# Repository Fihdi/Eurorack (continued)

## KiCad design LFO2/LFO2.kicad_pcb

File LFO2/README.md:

# Voltage controllable LFO/VCO

The core oscillator of this circuit is the same as in my TRIVCO module, an OTA-based relaxation oscillator, so this module can be used as a VCO as well.

The triangle output is strictly above 0V while the inverted triangle output is centered to 0V. The triangle output is strictly positive so I can reliably pull it down to 0V with the RESET input.

No more shape control, only way to get a sawtooth signal is to connect its square-wave output into the RESET input.

The module that you see in the picture above is using circuit boards that were fabricated by [PCBWay](https://www.pcbway.com/). They have excellent build quality and I can recommend using their service to build your own projects! I used the "Black" option for the soldermask and the surface has very deep and glossy black finish, which looks amazing, they also have an option for a "Matte Black" finish which I will try next time. Thank you PCBWay for sponsoring this module. Their website is very intuitive to use, just upload the gerber files as a .zip-file, tick the options such as base material, board width, my favorite feature: separate colors for the soldermask and silkscreen, surface finish etc. With multiple options for payment and fast delivery fast times I was able to put the entire project together in less than one month.

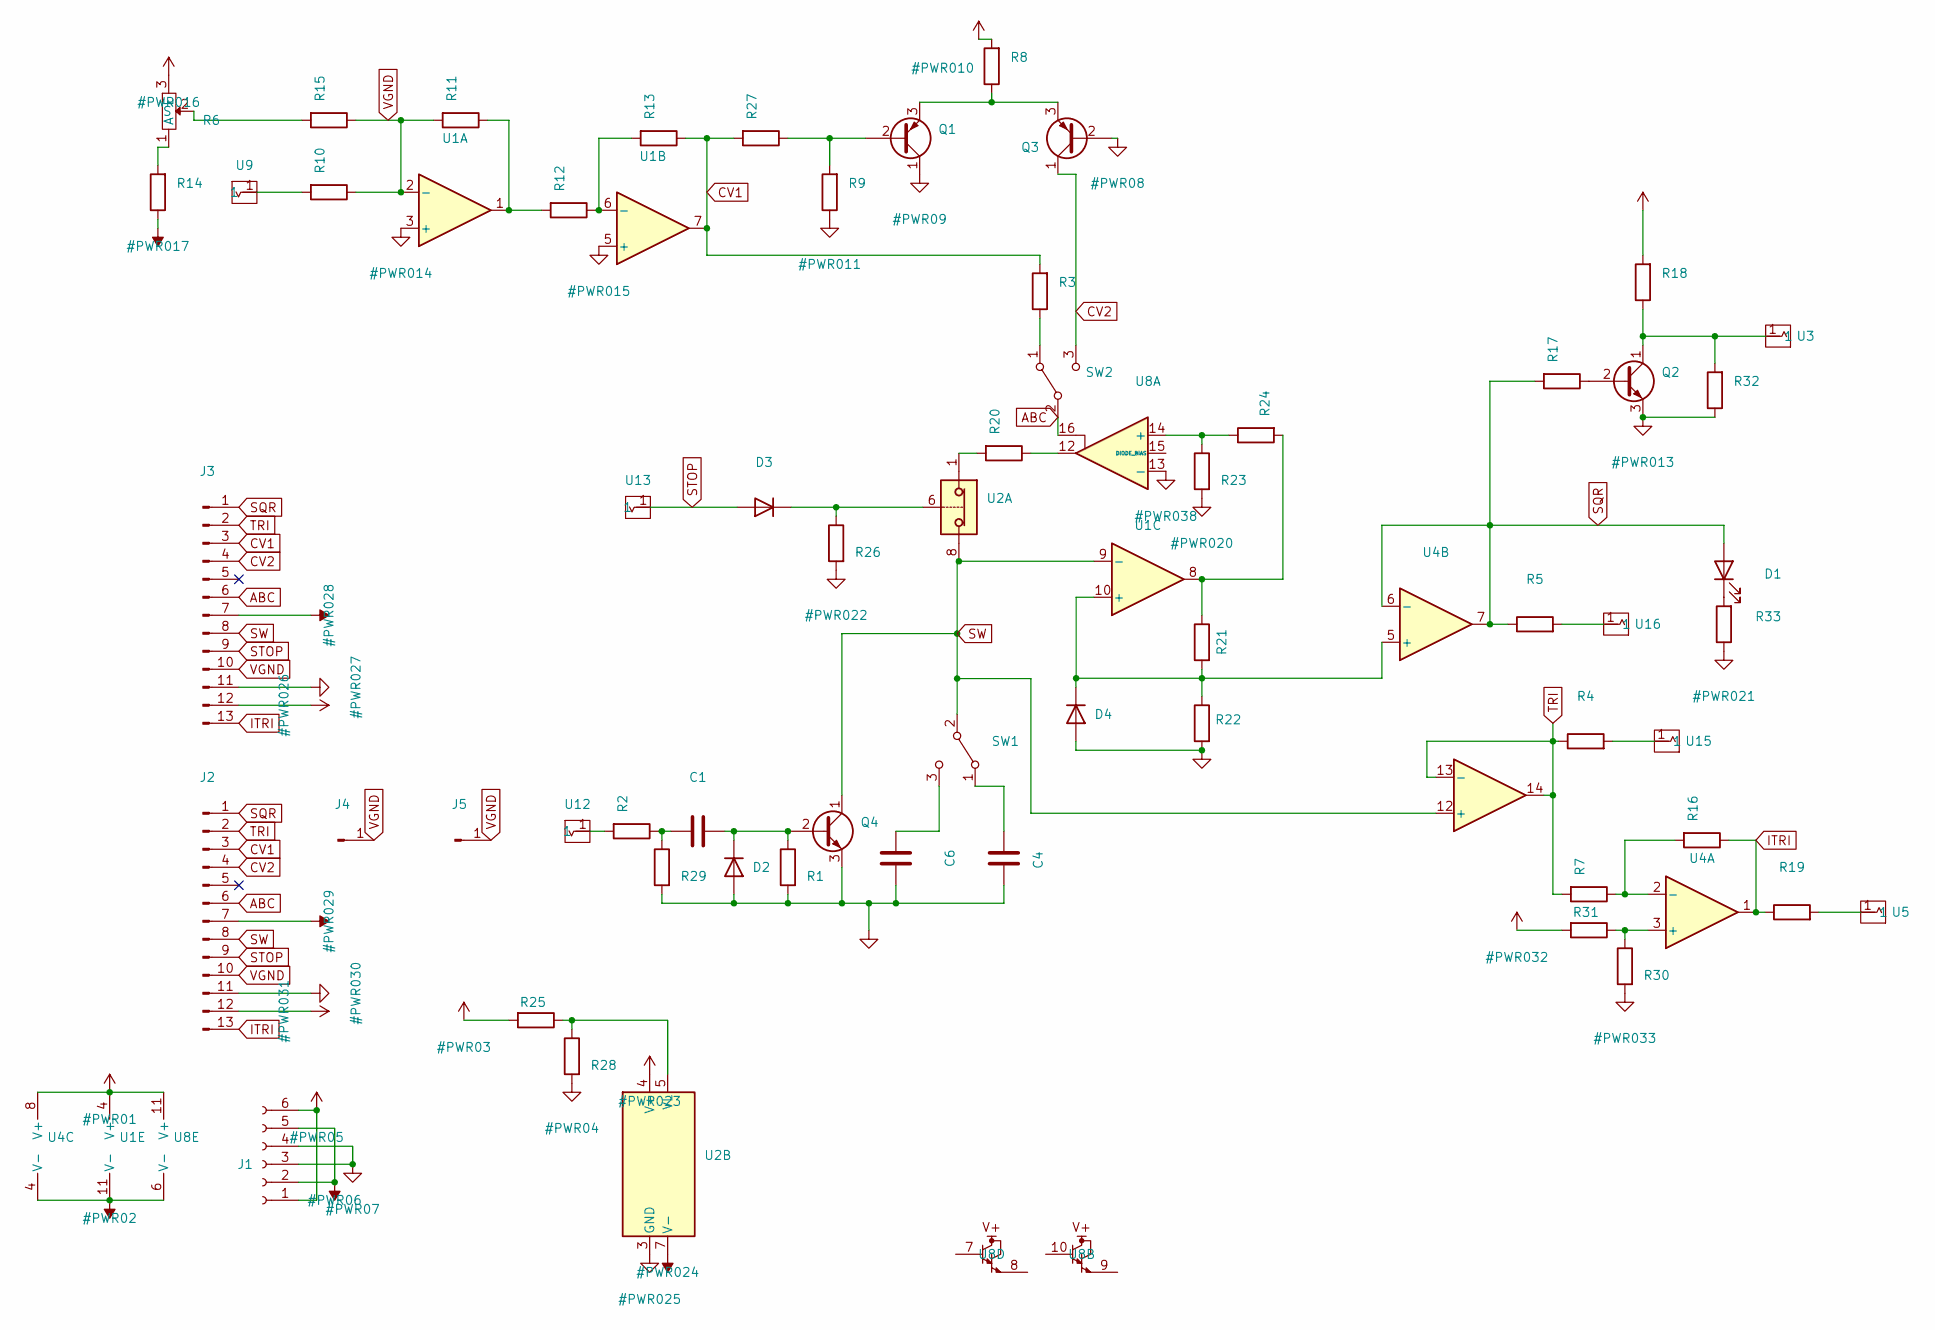
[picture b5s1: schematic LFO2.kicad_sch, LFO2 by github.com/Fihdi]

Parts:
C1, C4, C6: C; C_Axial_L3.8mm_D2.6mm_P10.00mm_Horizontal
D1: LED; LED_D5.0mm
D2, D3, D4: D; D_A-405_P7.62mm_Horizontal
J1: Conn_01x06_Female; PinHeader_1x06_P2.54mm_Vertical
J2, J3: Conn_01x13_Pin; PinHeader_1x13_P2.54mm_Vertical
J4, J5: Conn_01x01_Pin; PinHeader_1x01_P2.54mm_Vertical
Q1, Q3: BC557; TO-92L_Wide
Q2, Q4: BC547; TO-92L_Inline_Wide
R1, R7, R10, R11, R12, R13, R15, R16, R17, R21, R22, R24, R25, R26, R28, R29, R30, R31: 100k; R_Axial_DIN0204_L3.6mm_D1.6mm_P7.62mm_Horizontal
R2, R9, R14, R18, R20, R27, R32, R33: 4k7; R_Axial_DIN0204_L3.6mm_D1.6mm_P7.62mm_Horizontal
R3, R8: 10k; R_Axial_DIN0204_L3.6mm_D1.6mm_P7.62mm_Horizontal
R4, R5, R19, R23: 1k; R_Axial_DIN0204_L3.6mm_D1.6mm_P7.62mm_Horizontal
R6: 50k; AlpsPot
SW1, SW2: SW_SPDT; Switch
U1: TL074; DIP-14_W7.62mm
U2: DG417xJ; DIP-8_W7.62mm
U3, U5, U9, U12, U13, U15, U16: Aux_flush; 3mm5 Mono Aux
U4: TL072; DIP-8_W7.62mm
U8: LM13700; DIP-16_W7.62mm

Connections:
+12V: J1.1, J1.6, J2.12, J3.12, R6.3 (E), R8.2, R18.2, R25.2, R31.2, U1.4 (V+), U2.4 (V+), U4.8 (V+), U8.11 (V+)
-12V: J1.2, J1.5, J2.7, J3.7, R14.1, U1.11 (V-), U2.7 (V-), U4.4 (V-), U8.6 (V-)
ABC: J2.6, J3.6, SW2.2 (B), U8.16
CV1: J2.3, J3.3, R3.2, R13.1, R27.2, U1.7
CV2: J2.4, J3.4, Q3.1 (C), SW2.3 (C)
GND: C4.2, C6.2, D2.2 (A), D4.2 (A), J1.3, J1.4, J2.11, J3.11, Q1.1 (C), Q2.3 (E), Q3.2 (B), Q4.3 (E), R1.2, R9.1, R22.2, R23.2, R26.2, R28.2, R29.2, R30.2, R32.1, R33.1, U1.3 (+), U1.5 (+), U2.3 (GND), U8.13 (-)
ITRI: J2.13, J3.13, R16.1, R19.1, U4.1
unnamed: C1.1, R2.1, R29.1
unnamed: D1.1 (K), R33.2
unnamed: C1.2, D2.1 (K), Q4.2 (B), R1.1
unnamed: D3.1 (K), R26.1, U2.6
unnamed: D4.1 (K), R21.2, R22.1, U1.10 (+), U4.5 (+)
unnamed: Q1.2 (B), R9.2, R27.1
unnamed: Q1.3 (E), Q3.3 (E), R8.1
unnamed: Q2.2 (B), R17.1
unnamed: Q2.1 (C), R18.1, R32.2, U3.1
unnamed: R2.2, U12.1
unnamed: R4.2, U15.1
unnamed: R5.2, U16.1
unnamed: R6.1 (A), R14.2
unnamed: R6.2 (S), R15.2
unnamed: R10.2, U9.1
unnamed: R11.1, R12.2, U1.1
unnamed: R19.2, U5.1
unnamed: R20.1, U8.12
unnamed: R20.2, U2.1
unnamed: R21.1, R24.2, U1.8
unnamed: C4.1, SW1.1 (A)
unnamed: C6.1, SW1.3 (C)
unnamed: R3.1, SW2.1 (A)
unnamed: R12.1, R13.2, U1.6 (-)
unnamed: R25.1, R28.1, U2.5 (VL)
unnamed: R30.1, R31.1, U4.3 (+)
unnamed: R7.1, R16.2, U4.2 (-)
unnamed: R23.1, R24.1, U8.14 (+)
SQR: D1.2 (A), J2.1, J3.1, R5.1, R17.2, U4.6 (-), U4.7
STOP: D3.2 (A), J2.9, J3.9, U13.1
SW: J2.8, J3.8, Q4.1 (C), SW1.2 (B), U1.9 (-), U1.12 (+), U2.8
TRI: J2.2, J3.2, R4.1, R7.2, U1.13 (-), U1.14
VGND: J2.10, J3.10, J4.1, J5.1, R10.1, R11.2, R15.1, U1.2 (-)

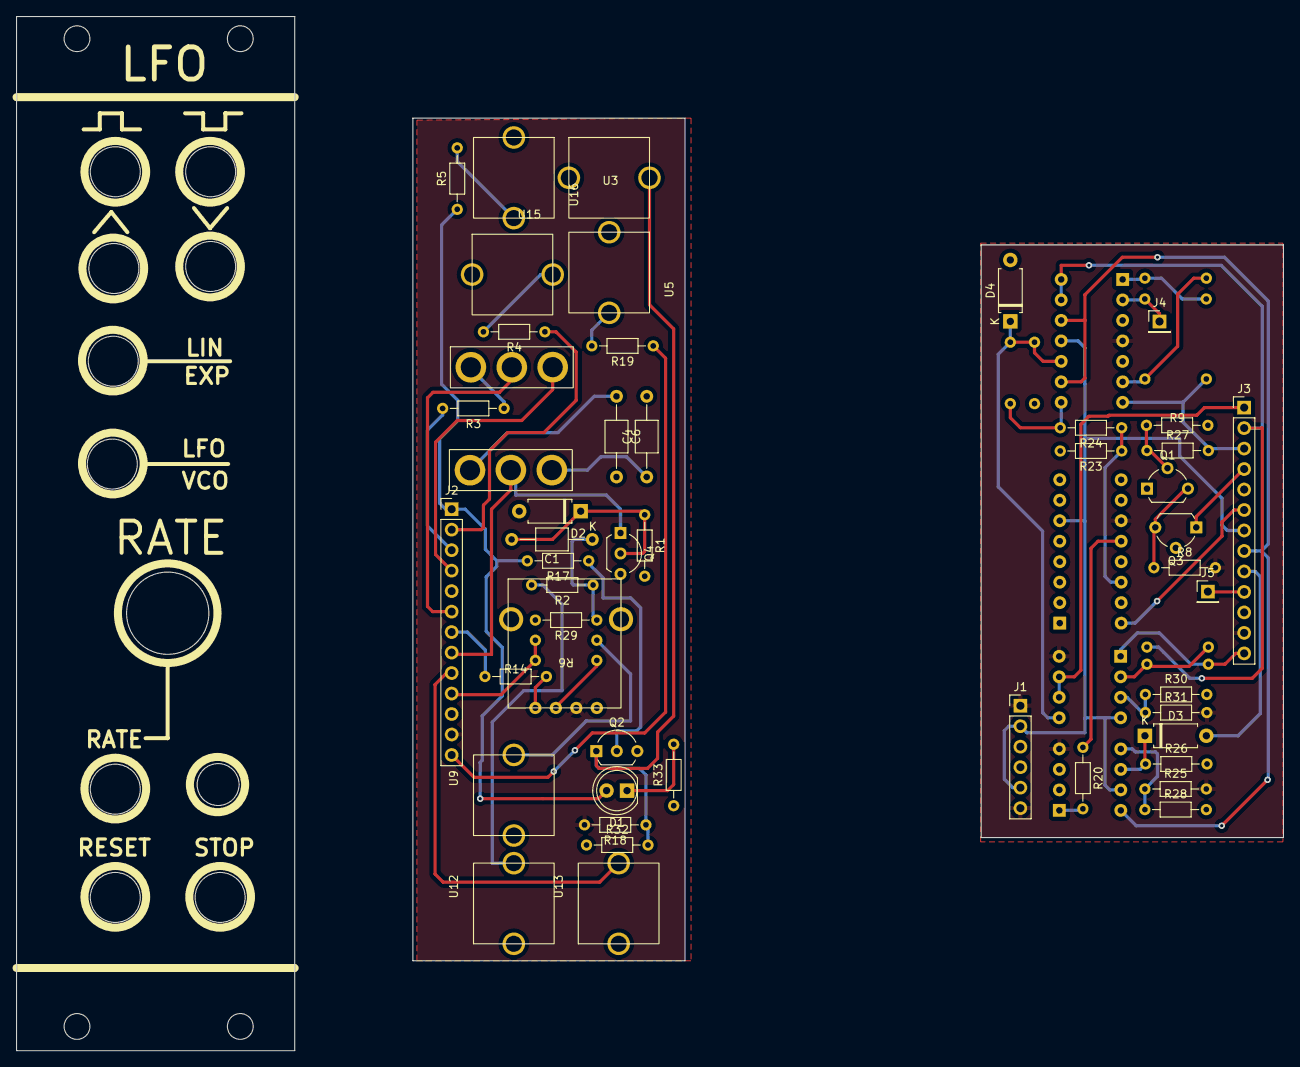
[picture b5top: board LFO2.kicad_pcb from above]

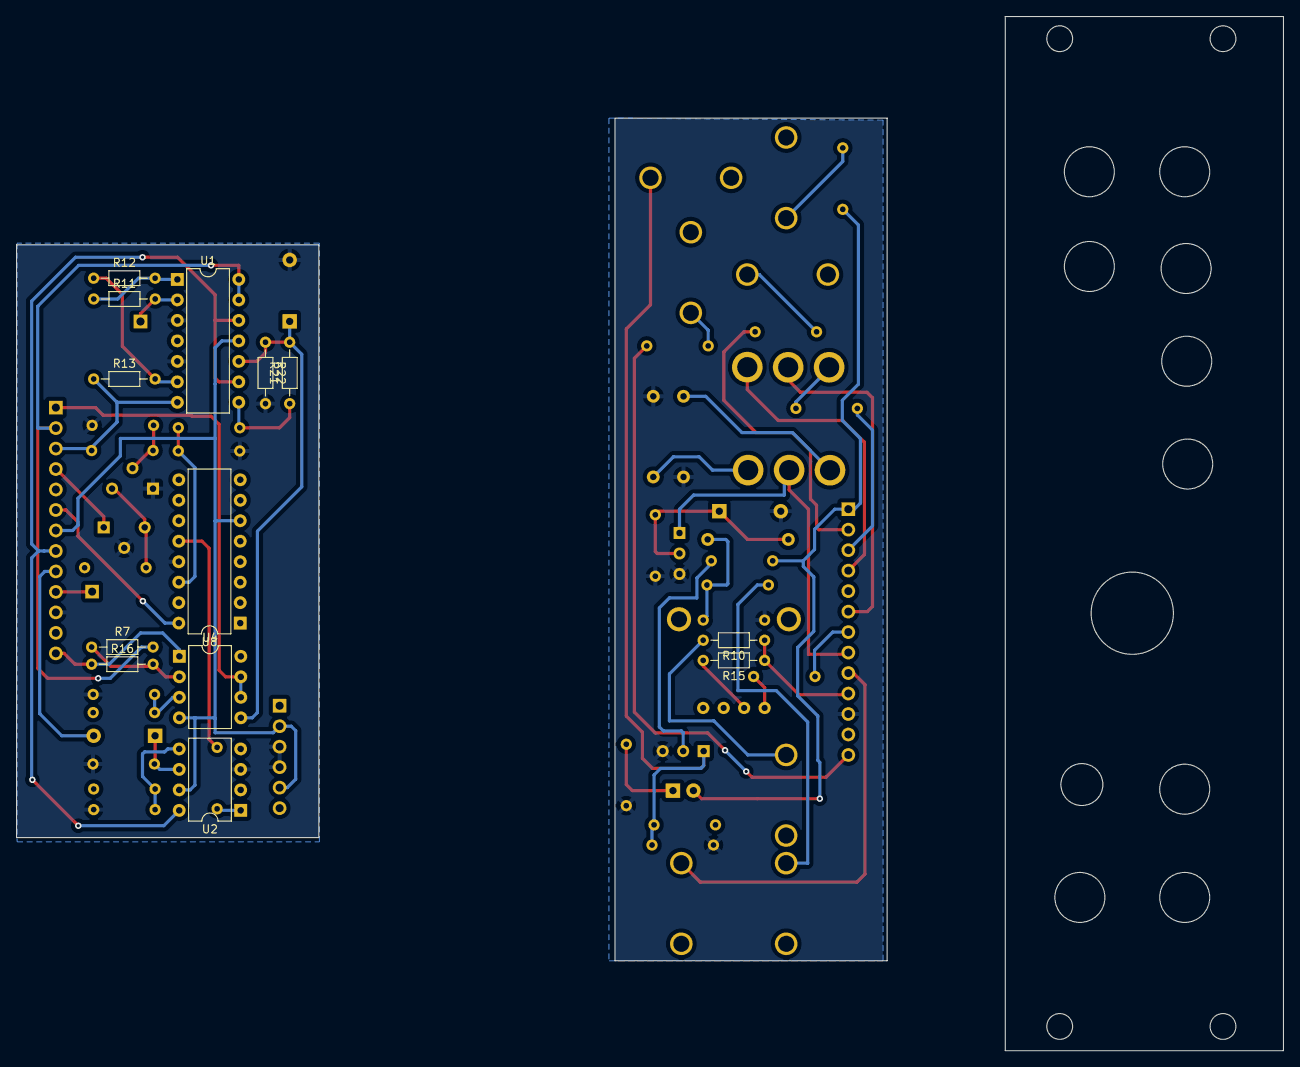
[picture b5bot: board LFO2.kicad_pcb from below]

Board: 2 copper layers, 157.1 x 128.2 mm, 62 parts (13 on the bottom side), 40 nets.

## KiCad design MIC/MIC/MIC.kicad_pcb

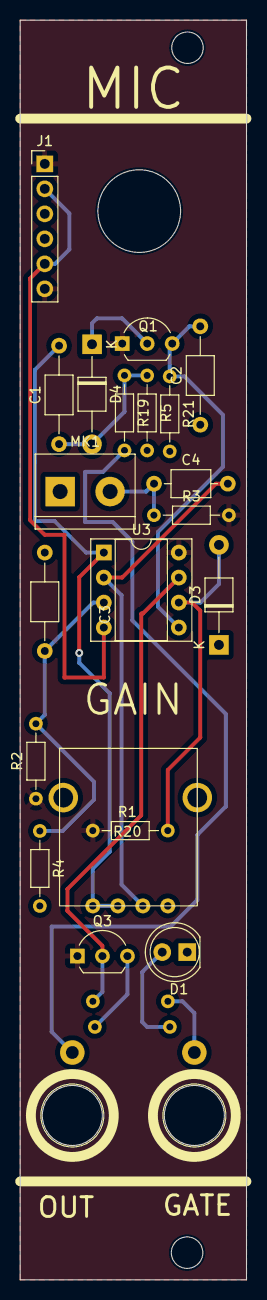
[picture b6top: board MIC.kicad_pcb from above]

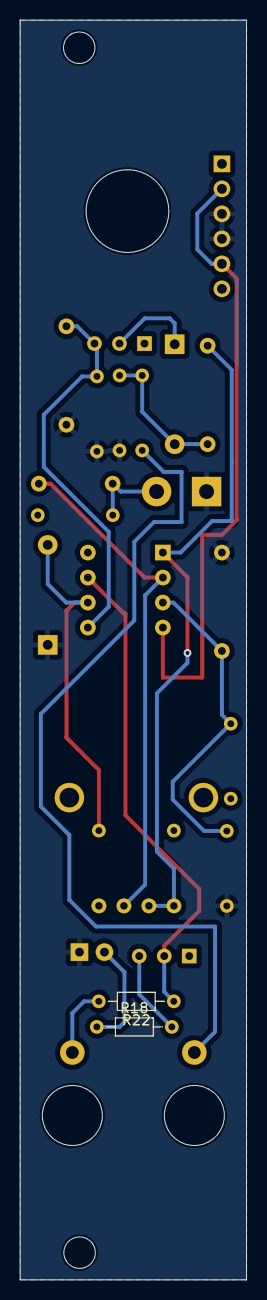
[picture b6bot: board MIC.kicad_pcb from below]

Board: 2 copper layers, 23.0 x 128.0 mm, 24 parts (2 on the bottom side), 16 nets.

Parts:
C1, C2, C3: C; C_Axial_L3.8mm_D2.6mm_P10.00mm_Horizontal
C4: C; C_Axial_L3.8mm_D2.6mm_P7.50mm_Horizontal
D1: LED; LED_D5.0mm
D3, D4: D; D_T-1_P10.16mm_Horizontal
J1: Conn_01x06_Pin; PinHeader_1x06_P2.54mm_Vertical
MK1: Microphone; TerminalBlock_bornier-2_P5.08mm
Q1, Q3: BC547; TO-92L_Inline_Wide
R1: AlpsPot
R2, R3, R4, R5, R18, R19, R20, R21, R22: R; R_Axial_DIN0204_L3.6mm_D1.6mm_P7.62mm_Horizontal
U1, U2: Aux_flush; aux_flush
U3: TL072; DIP-8_W7.62mm_Socket

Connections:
+12V: J1.1, J1.6, Q1.1 (C), Q3.1 (C), R2.1, R3.2, R20.2, U3.8 (V+)
-12V: J1.2, J1.5, U3.4 (V-)
GND: C2.1, C3.1, D1.1 (K), D3.1 (K), J1.3, J1.4, MK1.1 (-), R4.2, R5.2, R21.2
unnamed: D1.2 (A), R18.1
unnamed: D3.2 (A), R20.1, U3.6 (-)
unnamed: C1.1, D4.2 (A), R5.1, R19.1
unnamed: D4.1 (K), Q1.2 (B)
unnamed: C4.1, MK1.2 (+), R3.1
unnamed: C2.2, Q1.3 (E), R21.1, U3.5 (+)
unnamed: Q3.2 (B), R22.1, U3.7
unnamed: Q3.3 (E), R18.2
unnamed: C1.2, R1.1 (A), R1.2 (S), U3.1
unnamed: C4.2, R1.3 (E), U3.2 (-)
unnamed: R19.2, U1.1
unnamed: R22.2, U2.1
unnamed: C3.2, R2.2, R4.1, U3.3 (+)

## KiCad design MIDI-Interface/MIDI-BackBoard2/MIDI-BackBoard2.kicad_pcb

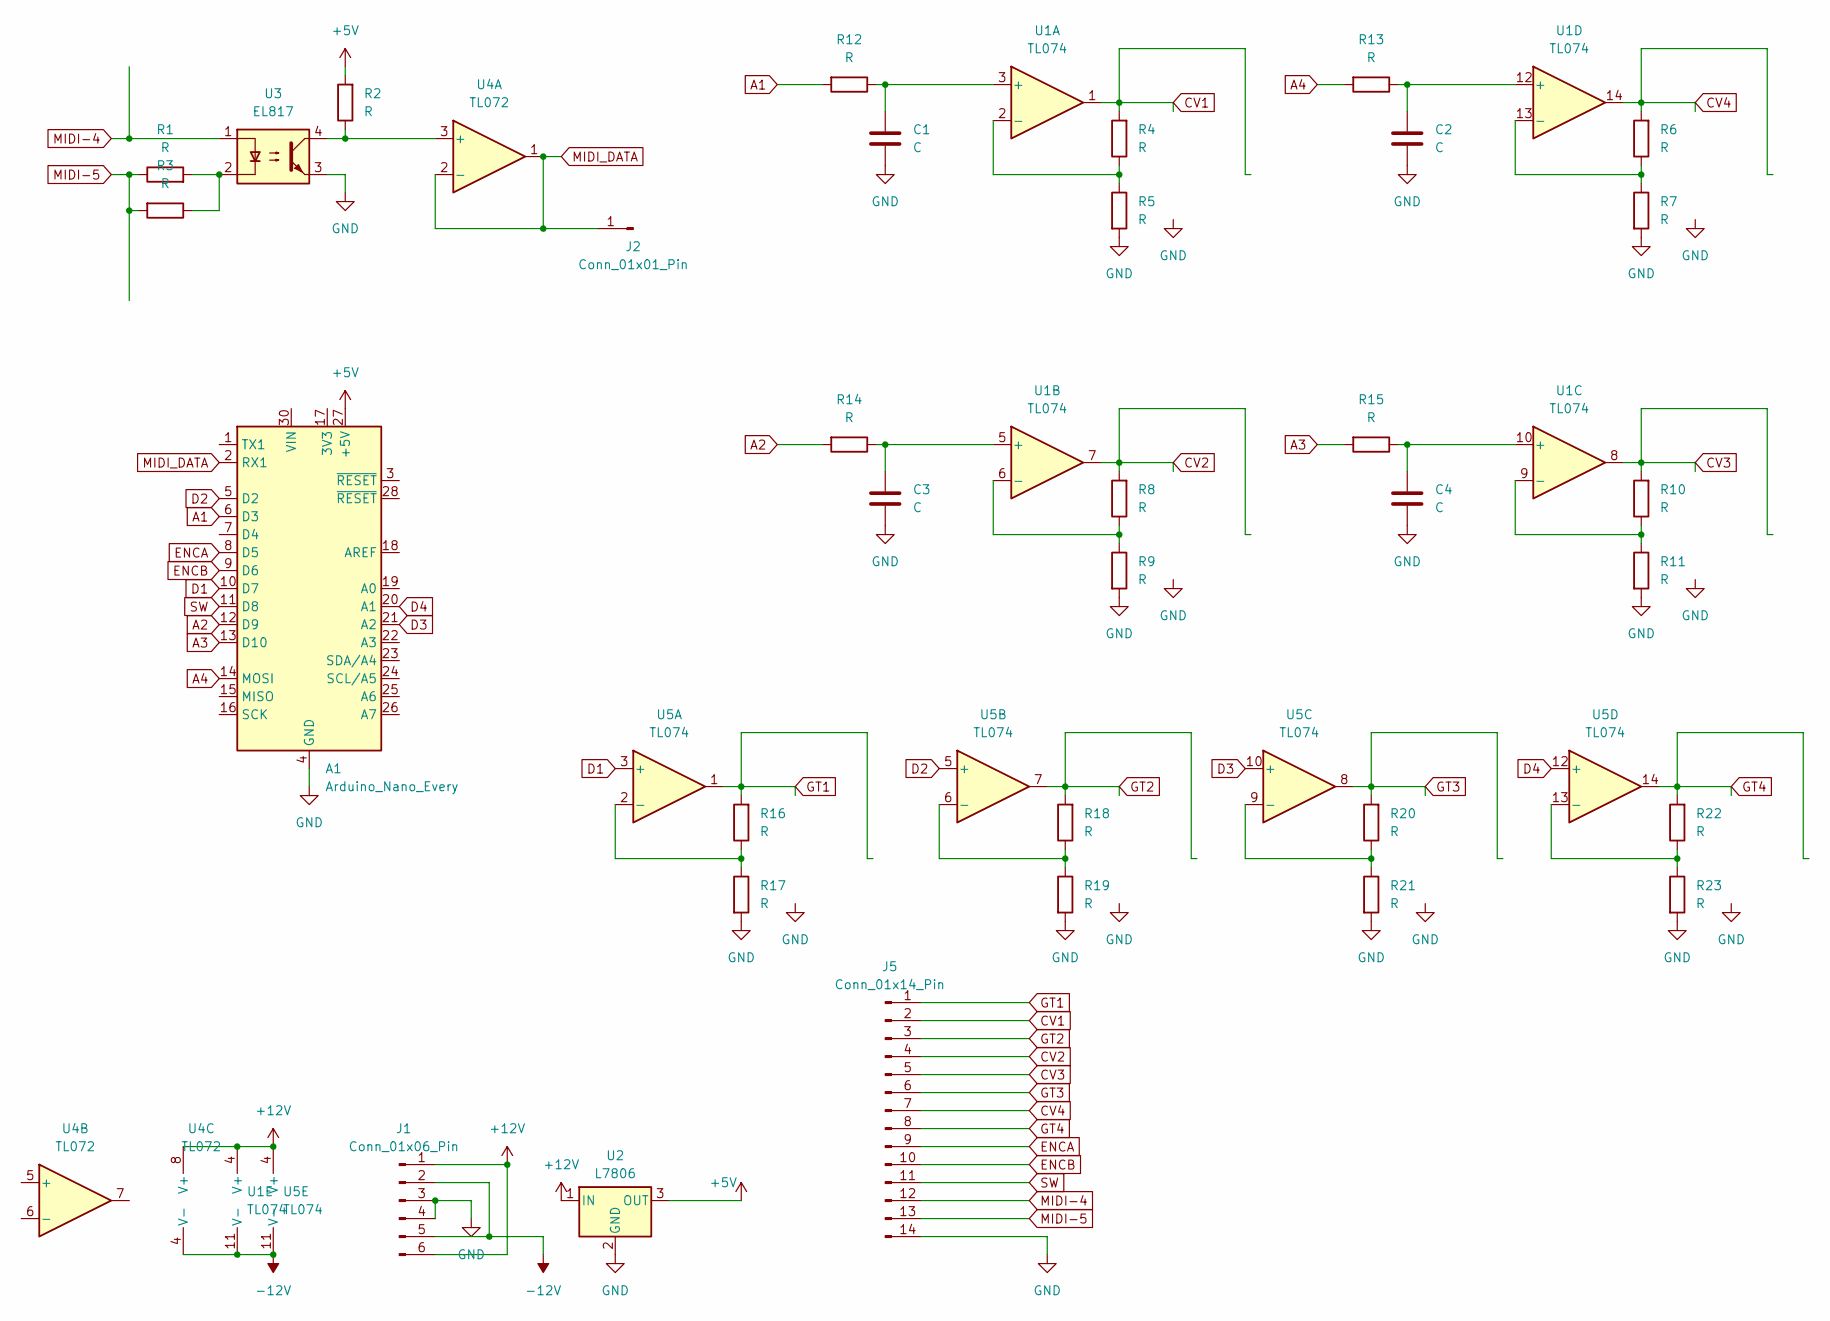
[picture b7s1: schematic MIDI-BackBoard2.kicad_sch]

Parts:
A1: Arduino_Nano_Every; Arduino_Nano
C1, C2, C3, C4: C; C_Rect_L7.0mm_W2.5mm_P5.00mm
J1: Conn_01x06_Pin; PinSocket_1x06_P2.54mm_Vertical
J2: Conn_01x01_Pin; PinHeader_1x01_P2.54mm_Vertical
J5: Conn_01x14_Pin; PinHeader_1x14_P2.54mm_Vertical
R1, R2, R3, R4, R5, R6, R7, R8, R9, R10, R11, R12, R13, R14, R15, R16, R17, R18, R19, R20, R21, R22, R23: R; R_Axial_DIN0207_L6.3mm_D2.5mm_P7.62mm_Horizontal
U1: TL074; DIP-14_W7.62mm_Socket
U2: L7806; TO-252-3_TabPin2
U3: EL817; DIP-4_W7.62mm
U4: TL072; DIP-8_W7.62mm
U5: TL074; DIP-14_W7.62mm

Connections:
+5V: A1.27 (+5V), R2.2, U2.3 (OUT)
+12V: J1.1, J1.6, U1.4 (V+), U2.1 (IN), U4.8 (V+), U5.4 (V+)
-12V: J1.2, J1.5, U1.11 (V-), U4.4 (V-), U5.11 (V-)
A1: A1.6 (D3), R12.2
A2: A1.12 (D9), R14.2
A3: A1.13 (D10), R15.2
A4: A1.14 (MOSI), R13.2
CV1: J5.2, R4.2, U1.1
CV2: J5.4, R8.2, U1.7
CV3: J5.5, R10.2, U1.8
CV4: J5.7, R6.2, U1.14
D1: A1.10 (D7), U5.3 (+)
D2: A1.5 (D2), U5.5 (+)
D3: A1.21 (A2), U5.10 (+)
D4: A1.20 (A1), U5.12 (+)
ENCA: A1.8 (D5), J5.9
ENCB: A1.9 (D6), J5.10
GND: A1.4 (GND), A1.29 (GND), C1.2, C2.2, C3.2, C4.2, J1.3, J1.4, J5.14, R5.2, R7.2, R9.2, R11.2, R17.2, R19.2, R21.2, R23.2, U2.2 (GND), U3.3
GT1: J5.1, R16.2, U5.1
GT2: J5.3, R18.2, U5.7
GT3: J5.6, R20.2, U5.8
GT4: J5.8, R22.2, U5.14
MIDI-4: J5.12, U3.1
MIDI-5: J5.13, R1.1, R3.2
MIDI_DATA: A1.2 (RX1), J2.1, U4.1, U4.2 (-)
unnamed: R1.2, R3.1, U3.2
unnamed: C1.1, R12.1, U1.3 (+)
unnamed: R4.1, R5.1, U1.2 (-)
unnamed: C3.1, R14.1, U1.5 (+)
unnamed: R8.1, R9.1, U1.6 (-)
unnamed: C4.1, R15.1, U1.10 (+)
unnamed: R10.1, R11.1, U1.9 (-)
unnamed: C2.1, R13.1, U1.12 (+)
unnamed: R6.1, R7.1, U1.13 (-)
unnamed: R2.1, U3.4, U4.3 (+)
unnamed: R16.1, R17.1, U5.2 (-)
unnamed: R18.1, R19.1, U5.6 (-)
unnamed: R20.1, R21.1, U5.9 (-)
unnamed: R22.1, R23.1, U5.13 (-)
SW: A1.11 (D8), J5.11

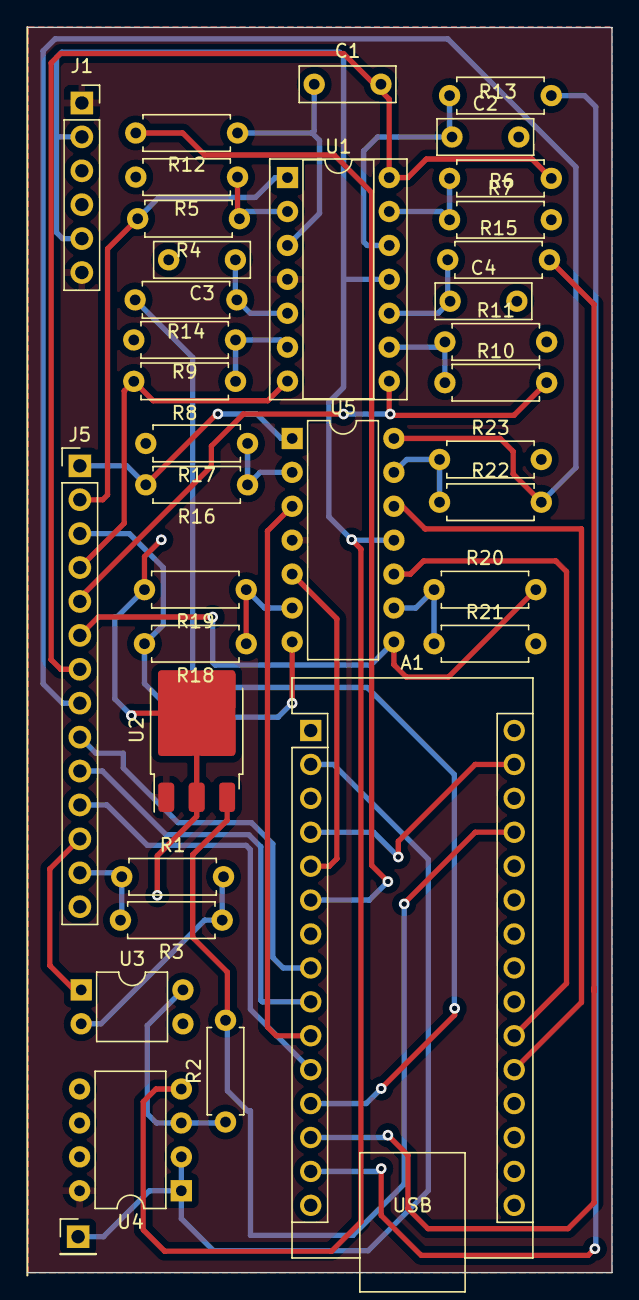
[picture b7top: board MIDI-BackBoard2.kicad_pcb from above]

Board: 2 copper layers, 43.8 x 93.3 mm, 36 parts (0 on the bottom side), 40 nets.
